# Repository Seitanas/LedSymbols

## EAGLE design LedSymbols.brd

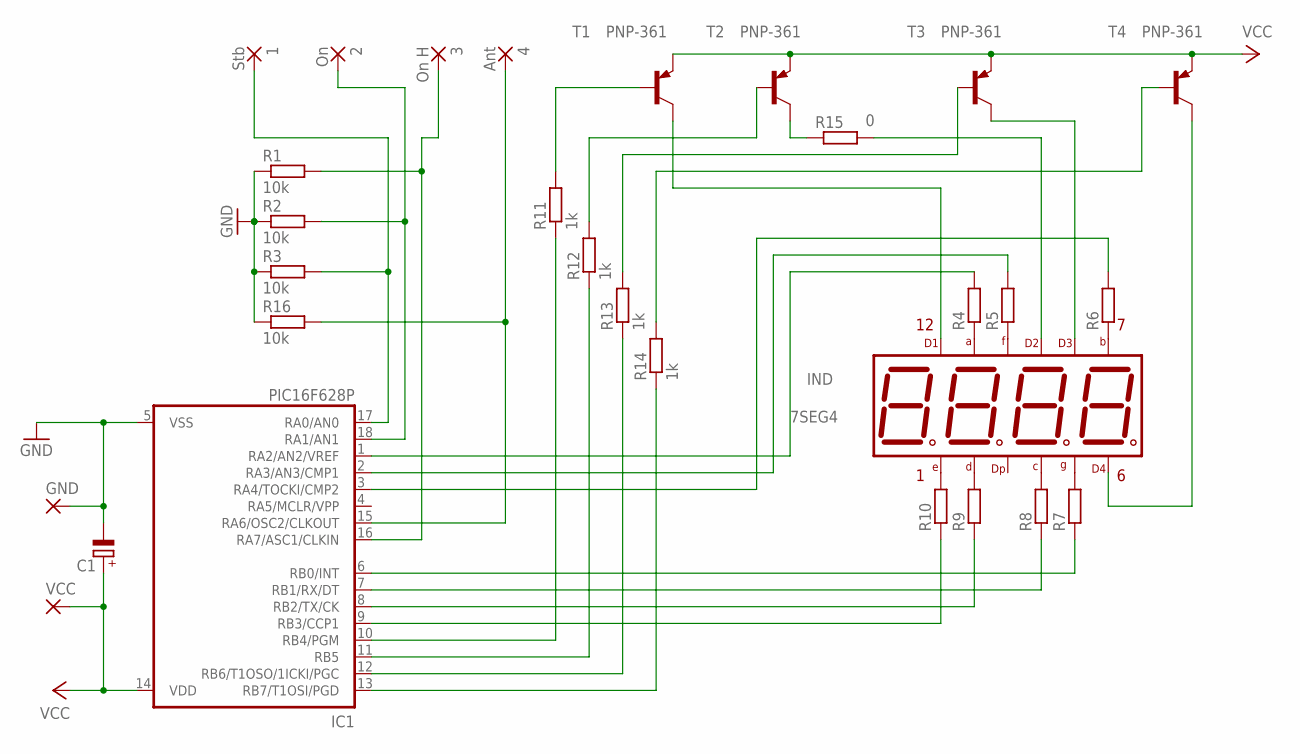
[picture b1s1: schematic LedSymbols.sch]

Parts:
1: Stb; 1,6/0,8
2: On; 1,6/0,8
3: On H; 1,6/0,8
4: Ant; 1,6/0,8
C1: CPOL-EUSMCC; SMC_C
GND: 2,15/1,0
IC1: PIC16F628P; DIL18
IND: 7SEG4
R1, R2, R3, R16: 10k; M0805
R4, R5, R6, R7, R8, R9, R10: R-EU_M0805; M0805
R11, R12, R13, R14: 1k; M0805
R15: 0; M1206
T1, T2, T3, T4: PNP-361
VCC: 2,15/1,0

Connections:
GND: C1.-, GND.1, IC1.5 (VSS), R1.1, R2.1, R3.1, R16.1
unnamed: IND.E, R10.2
unnamed: IND.D1, T1.C
unnamed: R14.2, T4.B
unnamed: IC1.6 (RB0/INT), R7.1
unnamed: IC1.7 (RB1/RX/DT), R8.1
unnamed: IND.D2, R15.2
unnamed: IND.D3, T3.C
unnamed: IND.D, R9.2
unnamed: IND.C, R8.2
unnamed: IND.G, R7.2
unnamed: IND.A, R4.1
unnamed: IND.F, R5.1
unnamed: IND.B, R6.1
unnamed: IND.D4, T4.C
unnamed: IC1.8 (RB2/TX/CK), R9.1
unnamed: IC1.10 (RB4/PGM), R11.1
unnamed: IC1.11 (RB5), R12.1
unnamed: R13.2, T3.B
unnamed: IC1.9 (RB3/CCP1), R10.1
unnamed: IC1.1 (RA2/AN2/VREF), R4.2
unnamed: 1.1, IC1.17 (RA0/AN0), R3.2
unnamed: 2.1, IC1.18 (RA1/AN1), R2.2
unnamed: 3.1, IC1.16 (RA7/ASC1/CLKIN), R1.2
unnamed: IC1.2 (RA3/AN3/CMP1), R5.2
unnamed: IC1.3 (RA4/TOCKI/CMP2), R6.2
unnamed: R12.2, T2.B
unnamed: R11.2, T1.B
unnamed: IC1.12 (RB6/T1OSO/1ICKI/PGC), R13.1
unnamed: IC1.13 (RB7/T1OSI/PGD), R14.1
unnamed: R15.1, T2.C
unnamed: 4.1, IC1.15 (RA6/OSC2/CLKOUT), R16.2
VCC: C1.+, IC1.14 (VDD), T1.E, T2.E, T3.E, T4.E, VCC.1

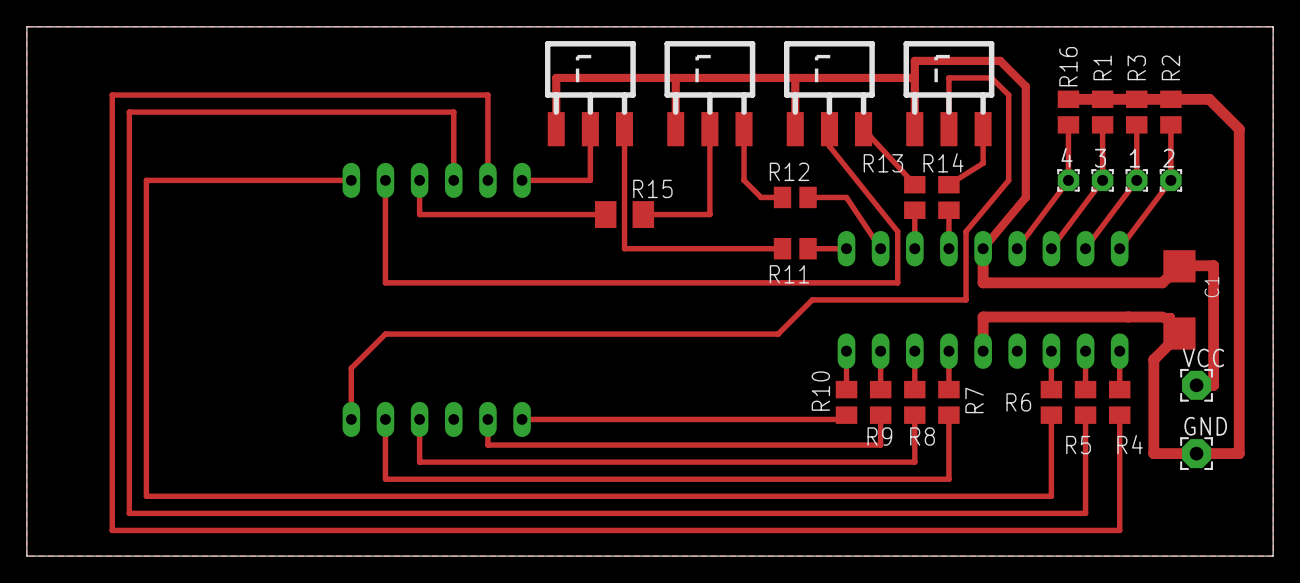
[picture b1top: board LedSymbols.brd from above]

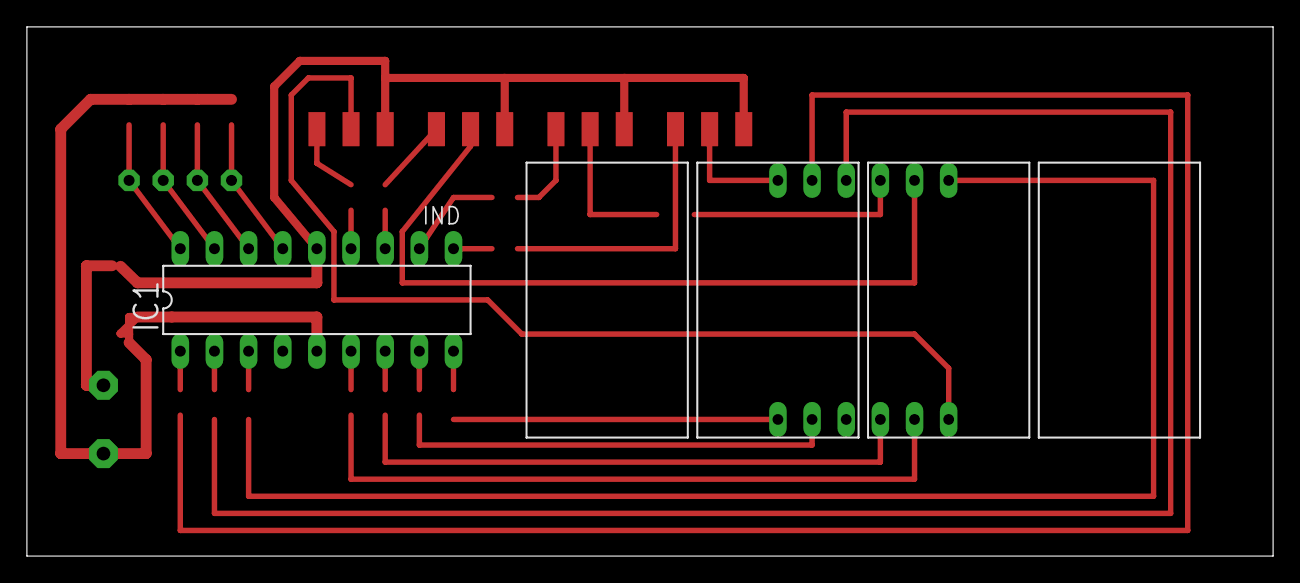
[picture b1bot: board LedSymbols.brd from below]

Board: 2 copper layers, 92.7 x 39.4 mm, 29 parts (2 on the bottom side), 33 nets.

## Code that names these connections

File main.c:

#include <htc.h>
__CONFIG(FOSC_INTOSCIO & WDTE_OFF & PWRTE_OFF & MCLRE_OFF & BOREN_OFF & LVP_OFF & CPD_OFF & CP_OFF);
#define _XTAL_FREQ 4000000

#define LEDnr1 RB4
#define LEDnr2 RB5
#define LEDnr3 RB6
#define LEDnr4 RB7

#define Stb RA0
#define On  RA1
#define OnH RA7
#define Ant RA6

#define a RA2 
#define b RA4 
#define c RB1
#define d RB2
#define e RB3
#define f RA3
#define g RB0

void reset_led(void){
   LEDnr1=1;
   LEDnr2=1;
   LEDnr3=1; 
   LEDnr4=1; 
   a=1;
   b=1;
   c=1;
   d=1;
   e=1;
   f=1;
   g=1;    
}

void letter_A(void){
    a=0;
    b=0;
    c=0;
    e=0;
    f=0;
    g=0;
}

void letter_b(void){
   c=0;
   d=0;
   e=0;
   f=0;
   g=0;  
}

void letter_H(void){
    b=0;
    c=0;
    e=0;
    f=0;
    g=0;
}

void letter_n(void){
    a=1;
    b=1;
    c=0;
    d=1;
    e=0;
    f=1;
    g=0;
}

void letter_O(void){
    a=0;
    b=0;
    c=0;
    d=0;
    e=0;
    f=0;
}

void letter_S(void){
    a=0;
    c=0;
    d=0;
    f=0;
    g=0;
}

void letter_t(void){
    a=1;
    b=1;
    c=1;
    d=0;
    e=0;
    f=0;
    g=0;
}

void letter_space(void){
    a=1;
    b=1;
    c=1;
    d=1;
    e=1;
    f=1;
    g=1;
}

void draw_symbols(char symbols[4]){
    unsigned int i;
    for (i = 0; i < 4; i++){
        reset_led();
        switch (i){
            case 0:
                LEDnr1=0;
                break;
            case 1:
                LEDnr2=0;
                break;
            case 2:
                LEDnr3=0;
                break;
            case 3:
                LEDnr4=0;
                break;
        }
        switch (symbols[i]){
            case 'A':
               letter_A(); 
               break;
            case 'b':
               letter_b(); 
               break;
            case 'H':
               letter_H();
               break;
            case 'n':
               letter_n();
               break;
            case 'O':
               letter_O();
               break;
            case 'S':
               letter_S();
               break;
            case 't':
               letter_t();
               break;
            case ' ':
               letter_space();
               break;
            default:
               letter_space();
        }
        __delay_ms(1);        
    }  
    reset_led();
}
void main(void) {
    TMR1ON = 0; //disabling timer for RB6-RB7 to be able to go outputs
    CMCON = 0x07;
    
    TRISA0=1;
    TRISA1=1;
    TRISA2=0;
    TRISA3=0;
    TRISA4=0;
    TRISA5=0;
    TRISA6=1;
    TRISA7=1;
    
    TRISB0=0;
    TRISB1=0;
    TRISB2=0;
    TRISB3=0;
    TRISB4=0;
    TRISB5=0;
    TRISB6=0;
    TRISB7=0;
    reset_led();
    __delay_ms(1);
    while (1){
        if (On)
            draw_symbols("On  ");
        else if (Stb&&!On&&!OnH&&!Ant)
            draw_symbols("Stb ");
        else if (OnH)
            draw_symbols("On H"); 
        else if (Ant)
            draw_symbols("Ant ");
        reset_led();
    }
}

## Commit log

2017-01-12 Optimising code
2017-01-13 Updating scheme
2017-01-17 Remaking scheme and code
2017-01-22 Fixing code
2017-05-30 Create LICENSE
